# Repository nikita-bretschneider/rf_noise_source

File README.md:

# RF Noise Generator

Simple RF noise generator. Documentation avaiable only in czech language.
English version is coming soon. 

see https://github.com/nikita-bretschneider/rf_noise_source/blob/main/doc/rf_noise_source_doc.pdf

PC board fabrication data are in the fab/ folder. KiCAD project is in main directory.

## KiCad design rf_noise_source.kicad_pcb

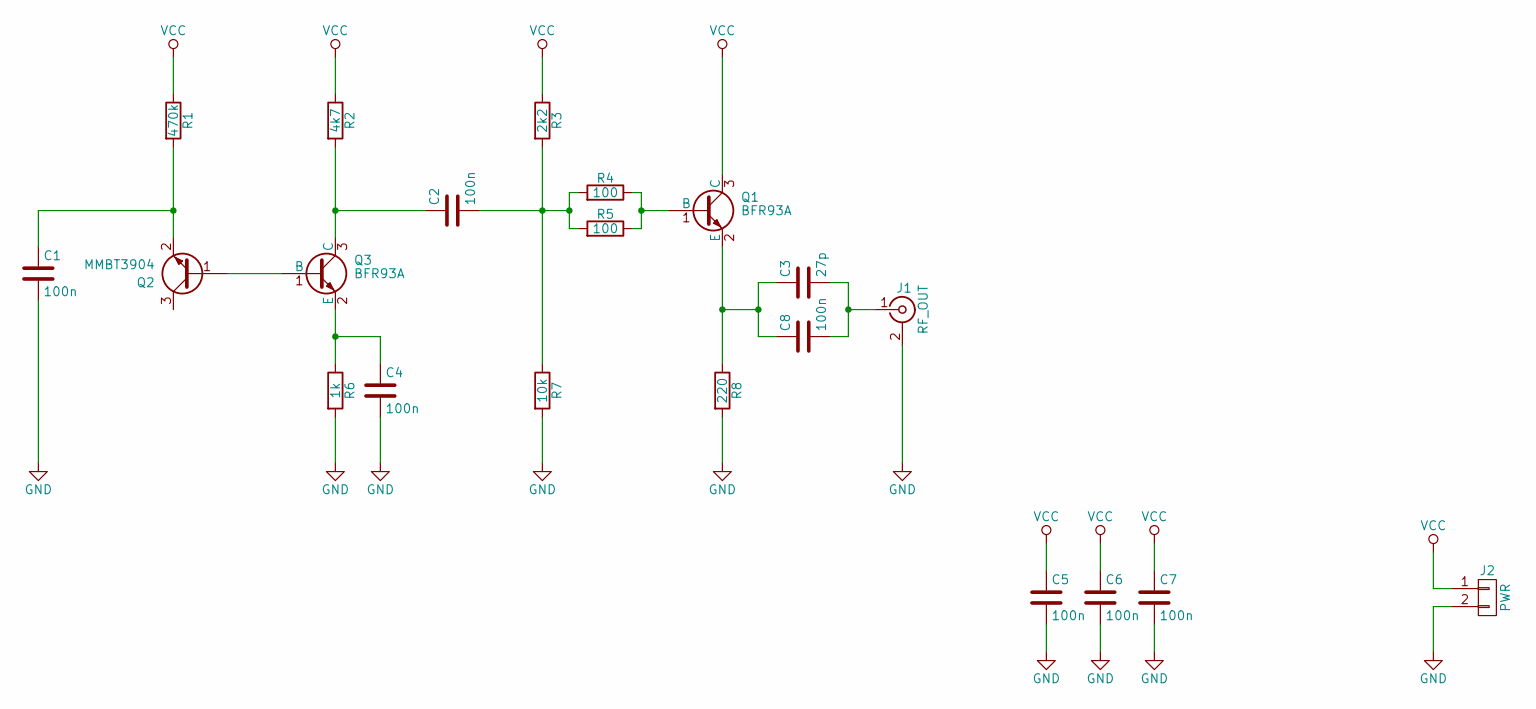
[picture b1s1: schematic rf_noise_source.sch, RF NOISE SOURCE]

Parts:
C1, C2, C4, C5, C6, C7, C8: 100n; C_0805
C3: 27p; C_0805
J1: RF_OUT; SMA-BRDEDGE
J2: PWR; Pin_Header_Straight_1x02_Pitch2.54mm_SMD_Pin1Left
Q1, Q3: BFR93A; SOT-23
Q2: MMBT3904; SOT-23
R1: 470k; R_0805
R2: 4k7; R_0805
R3: 2k2; R_0805
R4, R5: 100; R_0805
R6: 1k; R_0805
R7: 10k; R_0805
R8: 220; R_0805

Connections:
GND: C1.2, C4.2, C5.2, C6.2, C7.2, J1.2 (Ext), J2.2, R6.2, R7.2, R8.2
unnamed: C1.1, Q2.2 (E), R1.2
unnamed: C2.1, Q3.3 (C), R2.2
unnamed: C2.2, R3.2, R4.2, R5.2, R7.1
unnamed: C3.1, C8.1, Q1.2 (E), R8.1
unnamed: C3.2, C8.2, J1.1 (In)
unnamed: C4.1, Q3.2 (E), R6.1
unnamed: Q1.1 (B), R4.1, R5.1
unnamed: Q2.1 (B), Q3.1 (B)
VCC: C5.1, C6.1, C7.1, J2.1, Q1.3 (C), R1.1, R2.1, R3.1

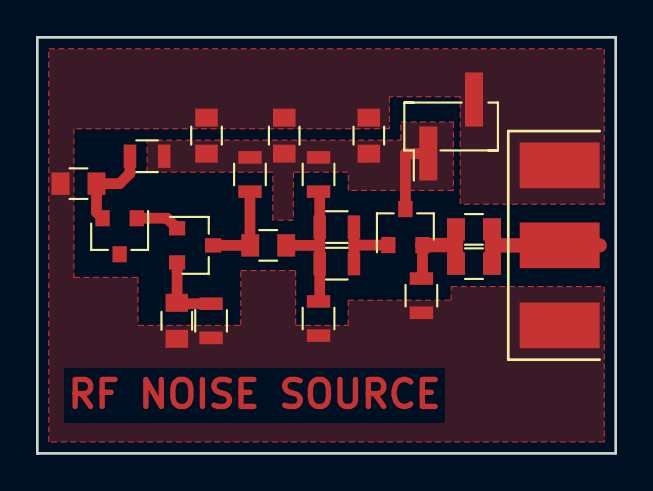
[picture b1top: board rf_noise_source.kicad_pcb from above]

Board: 2 copper layers, 32.1 x 23.1 mm, 21 parts (0 on the bottom side), 10 nets.

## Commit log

2021-07-17 2021-07-17
